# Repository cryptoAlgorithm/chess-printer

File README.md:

# Chess Printer

> A chess bot, but on steroids.

A completely custom-designed 3D printer control board with
an ESP32 MCU. Designed to control a CoreXY printer, but can
probably be adapted to any kinematic system.

> **Warning**: This is an experimental project with no gurantees - use at
> your own risk and discretion!

## Notable Features

* 6 stepper drivers (labelled X, Y, E0, Z1, Z2 & Z3)
  - Designed for TMC2209 drivers
  - 1-wire Serial communication with all drivers supported
* ATX & screw terminal power input
  - `PS-ON` control (standby & emergency kill poweroff supported in Marlin)
  - MCU can be powered from `5VSB` ATX power rail with jumper selection
    (**DO NOT** power via USB and `5VSB` concurrently - doing so will almost definitely damage _something_!)
* ESP32 MCU (DevKit-C footprint)
* I2S stepper stream
  - 2x daisy-chained `75HC595` shift registers
* I2C LCD
* 1 hotend & 1 heatbed thermistor input
* 1 high power MOSFET bed heater & 1 heatbed output (for external relay/SSR)
* 1 controllable & 1 always-on fan output

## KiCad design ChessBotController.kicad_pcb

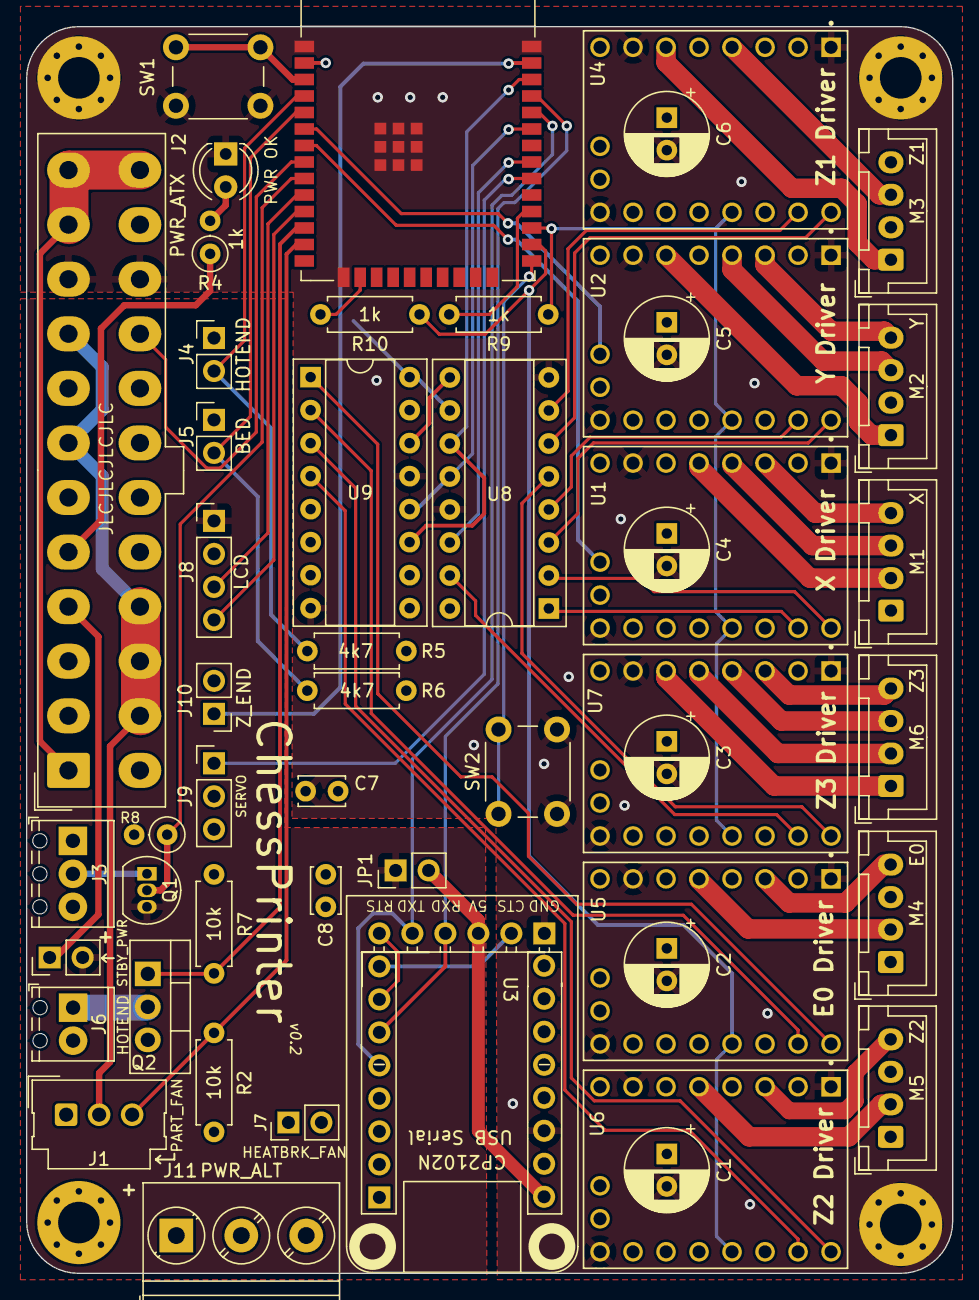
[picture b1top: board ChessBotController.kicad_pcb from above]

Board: 4 copper layers, 71.3 x 95.9 mm, 54 parts (0 on the bottom side), 73 nets.

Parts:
C1, C2, C3, C4, C5, C6: 100uF; CP_Radial_D6.3mm_P2.50mm
C7, C8: 0.1uF; C_Disc_D3.4mm_W2.1mm_P2.50mm
D2: PWR OK; LED_D4.0mm
H1, H2, H3, H4: MountingHole_Pad; MountingHole_3.2mm_M3_Pad_Via
J1: PART_FAN; Molex_SL_171971-0003_1x03_P2.54mm_Vertical
J2: PWR_ATX; Molex_Mini-Fit_Jr_ATX24
J3: HEATBED; TerminalBlock_Phoenix_MPT-0,5-3-2.54_1x03_P2.54mm_Horizontal
J4: HOTEND; PinHeader_1x02_P2.54mm_Vertical
J5: BED; PinHeader_1x02_P2.54mm_Vertical
J6: HOTEND; TerminalBlock_Phoenix_MPT-0,5-2-2.54_1x02_P2.54mm_Horizontal
J7: HEATBRK_FAN; PinHeader_1x02_P2.54mm_Vertical
J8: LCD; PinHeader_1x04_P2.54mm_Vertical
J9: SERVO; PinHeader_1x03_P2.54mm_Vertical
J10: Z_END; PinHeader_1x02_P2.54mm_Vertical
J11: PWR_ALT; TerminalBlock_Phoenix_PT-1,5-3-5.0-H_1x03_P5.00mm_Horizontal
JP1: USB_PWR; PinHeader_1x02_P2.54mm_Vertical
JP2: STBY_PWR; PinHeader_1x02_P2.54mm_Vertical
M1: X; JST_XH_B4B-XH-A_1x04_P2.50mm_Vertical
M2: Y; JST_XH_B4B-XH-A_1x04_P2.50mm_Vertical
M3: Z1; JST_XH_B4B-XH-A_1x04_P2.50mm_Vertical
M4: E0; JST_XH_B4B-XH-A_1x04_P2.50mm_Vertical
M5: Z2; JST_XH_B4B-XH-A_1x04_P2.50mm_Vertical
M6: Z3; JST_XH_B4B-XH-A_1x04_P2.50mm_Vertical
Q1: 2N3904; TO-92_Inline
Q2: IRLZ44N; TO-220-3_Vertical
R2, R7: 10k; R_Axial_DIN0207_L6.3mm_D2.5mm_P7.62mm_Horizontal
R4: 1k; R_Axial_DIN0207_L6.3mm_D2.5mm_P2.54mm_Vertical
R5, R6: 4k7; R_Axial_DIN0207_L6.3mm_D2.5mm_P7.62mm_Horizontal
R8: 10K; R_Axial_DIN0207_L6.3mm_D2.5mm_P2.54mm_Vertical
R9, R10: 1k; R_Axial_DIN0207_L6.3mm_D2.5mm_P7.62mm_Horizontal
SW1, SW2: SW_Push; SW_PUSH_6mm
U1, U2, U4, U5, U6, U7: MODULE_TMC2209_SILENTSTEPSTICK
U3: Adafruit-CH2102N-Friend
U8, U9: 74HC595; DIP-16_W7.62mm_Socket
U10: ESP32-WROOM-E; ESP32-WROOM-32E

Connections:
+3.3VP: J2.1 (+3.3V), J2.2 (+3.3V), J2.12 (+3.3V), J2.13 (+3.3V)
+3V3: C7.1, C8.1, R5.1, R6.1, U1.10 (VIO), U2.2 (MS1), U2.10 (VIO), U3.10 (3V3), U4.3 (MS2), U4.10 (VIO), U5.2 (MS1), U5.3 (MS2), U5.10 (VIO), U6.10 (VIO), U7.2 (MS1), U7.10 (VIO), U8.10 (~SRCLR), U8.16 (VCC), U9.10 (~SRCLR), U9.16 (VCC), U10.2 (3V3)
+5V: J8.1, JP1.1 (A), JP2.2 (B), Q1.3 (C)
+5VP: J1.2, J2.4 (+5V), J2.6 (+5V), J2.21 (+5V), J2.22 (+5V), J2.23 (+5V), J9.2, J11.2
+12V: C1.1, C2.1, C3.1, C4.1, C5.1, C6.1, J2.10 (+12V), J2.11 (+12V), J3.1, J6.2, J7.1, J11.1, U1.16 (VM), U2.16 (VM), U4.16 (VM), U5.16 (VM), U6.16 (VM), U7.16 (VM)
/BED_H: Q1.2 (B), R8.1, U10.9 (32K_XN/GPIO33/ADC1_CH5)
/DRIVER_UART_1: R9.2, U1.5 (TX), U2.5 (TX), U4.5 (TX), U7.5 (TX), U10.27 (GPIO16)
/DRIVER_UART_2: R10.2, U5.5 (TX), U6.5 (TX), U10.26 (ADC2_CH0/GPIO4)
/E_DIR: U5.8 (DIR), U9.1 (QB)
/E_STEP: U5.7 (STEP), U9.2 (QC)
/FAN_0: J1.3, R2.1, U10.13 (MTMS/GPIO14/ADC2_CH6)
/HOTEND_H: Q2.1 (G), R7.1, U10.12 (ADC2_CH7/GPIO27)
/I2S_BCK: U8.11 (SRCLK), U9.11 (SRCLK), U10.36 (GPIO22)
/I2S_DIN: U8.14 (SER), U10.31 (GPIO19)
/I2S_WCK: U8.12 (RCLK), U9.12 (RCLK), U10.33 (GPIO21)
/MCU_RXD: U3.5 (TXD), U3.20 (TXD), U10.34 (U0RXD/GPIO3)
/MCU_TXD: U3.4 (RXD), U3.19 (RXD), U10.35 (U0TXD/GPIO1)
/PS_ON: J2.16 (PS_ON#), U10.8 (32K_XP/GPIO32/ADC1_CH4)
/Power/PWR_OK: J2.8 (PWR_OK), R4.1
/SCL: J8.3, U10.10 (DAC_1/ADC2_CH8/GPIO25)
/SDA: J8.4, U10.11 (DAC_2/ADC2_CH9/GPIO26)
/SERVO: J9.1, U10.30 (GPIO18)
/TEMP_BED: J5.2, R6.2, U10.5 (SENSOR_VN/GPIO39/ADC1_CH3)
/TEMP_HOTEND: J4.2, R5.2, U10.4 (SENSOR_VP/GPIO36/ADC1_CH0)
/X_DIR: U1.8 (DIR), U8.2 (QC)
/X_MIN: U1.17 (DIAG), U10.7 (GPIO35/ADC1_CH7)
/X_STEP: U1.7 (STEP), U8.1 (QB)
/Y_DIR: U2.8 (DIR), U8.3 (QD)
/Y_MIN: U2.17 (DIAG), U10.6 (GPIO34/ADC1_CH6)
/Y_STEP: U2.7 (STEP), U8.4 (QE)
/Z2_DIR: U6.8 (DIR), U9.3 (QD)
/Z2_STEP: U6.7 (STEP), U9.4 (QE)
/Z3_DIR: U7.8 (DIR), U8.5 (QF)
/Z3_STEP: U7.7 (STEP), U8.15 (QA)
/Z_DIR: U4.8 (DIR), U8.6 (QG)
/Z_MIN: J10.1, U10.37 (GPIO23)
/Z_STEP: U4.7 (STEP), U8.7 (QH)
GND: C1.2, C2.2, C3.2, C4.2, C5.2, C6.2, C7.2, C8.2, D2.1 (K), H1.1, H2.1, H3.1, H4.1, J1.1, J2.3 (GND), J2.5 (GND), J2.7 (GND), J2.15 (GND), J2.17 (GND), J2.18 (GND), J2.19 (GND), J2.24 (GND), J3.3, J4.1, J5.1, J7.2, J8.2, J9.3, J10.2, J11.3, Q2.3 (S), R2.2, R7.2, R8.2, SW1.1, SW2.2, U1.1 (EN), U1.9 (GND), U1.15 (GND), U2.1 (EN), U2.9 (GND), U2.15 (GND), U3.1 (GND), U3.11 (GND), U4.1 (EN), U4.9 (GND), U4.15 (GND), U5.1 (EN), U5.9 (GND), U5.15 (GND), U6.1 (EN), U6.9 (GND), U6.15 (GND), U7.1 (EN), U7.9 (GND), U7.15 (GND), U8.8 (GND), U8.13 (~OE), U9.8 (GND), U9.13 (~OE), U10.1 (GND), U10.15 (GND), U10.38 (GND), U10.39 (GND_THERMAL)
unnamed: D2.2 (A), R4.2
unnamed: J2.9 (+5VSB), JP2.1 (A)
unnamed: J3.2, Q1.1 (E)
unnamed: J6.1, Q2.2 (D)
unnamed: JP1.2 (B), U3.3 (5V), U3.9 (5V)
unnamed: M1.2 (-), U1.13 (A1)
unnamed: M2.2 (-), U2.13 (A1)
unnamed: M3.2 (-), U4.13 (A1)
unnamed: M4.2 (-), U5.13 (A1)
unnamed: M5.2 (-), U6.13 (A1)
unnamed: M6.2 (-), U7.13 (A1)
unnamed: M1.1, U1.14 (A2)
unnamed: M1.3, U1.12 (B1)
unnamed: M1.4, U1.11 (B2)
unnamed: M2.1, U2.14 (A2)
unnamed: M2.3, U2.12 (B1)
unnamed: M2.4, U2.11 (B2)
unnamed: U3.8 (RTS), U3.18 (RTS)
unnamed: M3.1, U4.14 (A2)
unnamed: M3.3, U4.12 (B1)
unnamed: M3.4, U4.11 (B2)
unnamed: M4.1, U5.14 (A2)
unnamed: M4.3, U5.12 (B1)
unnamed: M4.4, U5.11 (B2)
unnamed: M5.1, U6.14 (A2)
unnamed: M5.3, U6.12 (B1)
unnamed: M5.4, U6.11 (B2)
unnamed: M6.1, U7.14 (A2)
unnamed: M6.3, U7.12 (B1)
unnamed: M6.4, U7.11 (B2)
unnamed: U8.9 (QH'), U9.14 (SER)
unnamed: SW1.2, U10.3 (EN/CHIP_PU)
unnamed: SW2.1, U10.25 (GPIO0/BOOT/ADC2_CH1)
unnamed: R9.1, U10.28 (GPIO17)
unnamed: R10.1, U10.16 (MTCK/GPIO13/ADC2_CH4)

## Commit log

2023-05-25 feat: initial commit
2023-06-22 patch: remove backups
2023-06-22 patch(gitignore): make backup ignore rule more specific
    patch: remove redundant copy of PCB with old design
2023-06-22 feat(README): create readme
2023-06-22 feat(README): upload assembled controller image
2023-06-22 feat(readme): update doc images
2023-06-22 feat(readme): add images
2023-06-26 feat: initial v0.2 design
